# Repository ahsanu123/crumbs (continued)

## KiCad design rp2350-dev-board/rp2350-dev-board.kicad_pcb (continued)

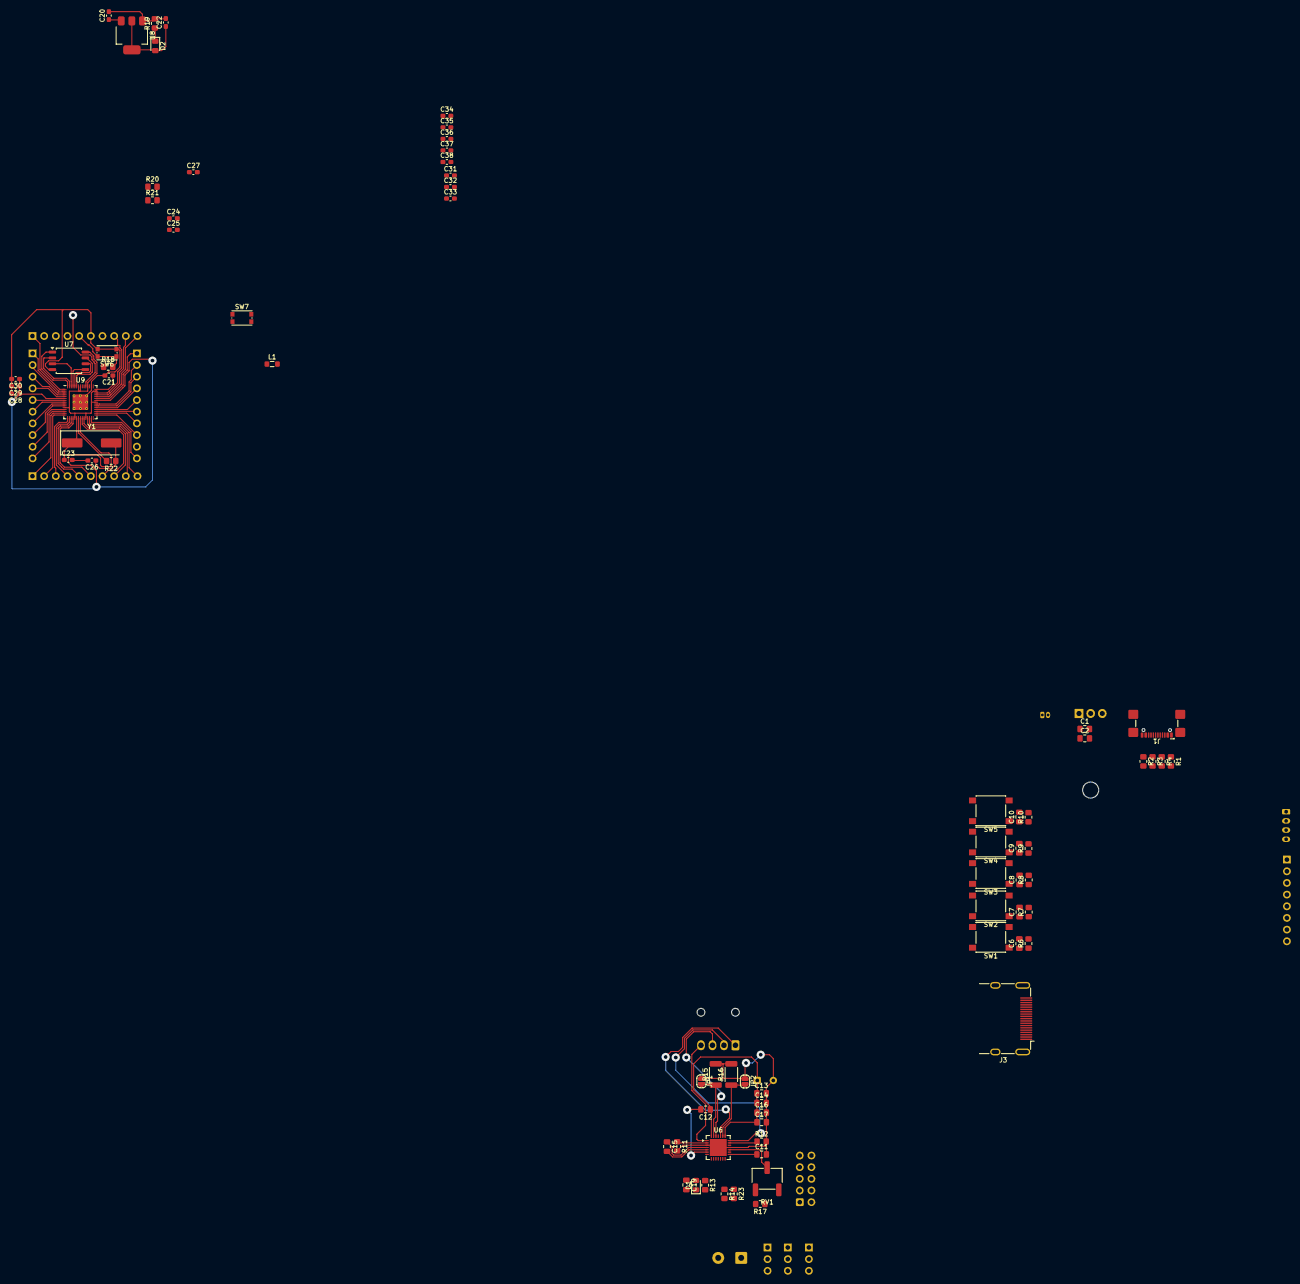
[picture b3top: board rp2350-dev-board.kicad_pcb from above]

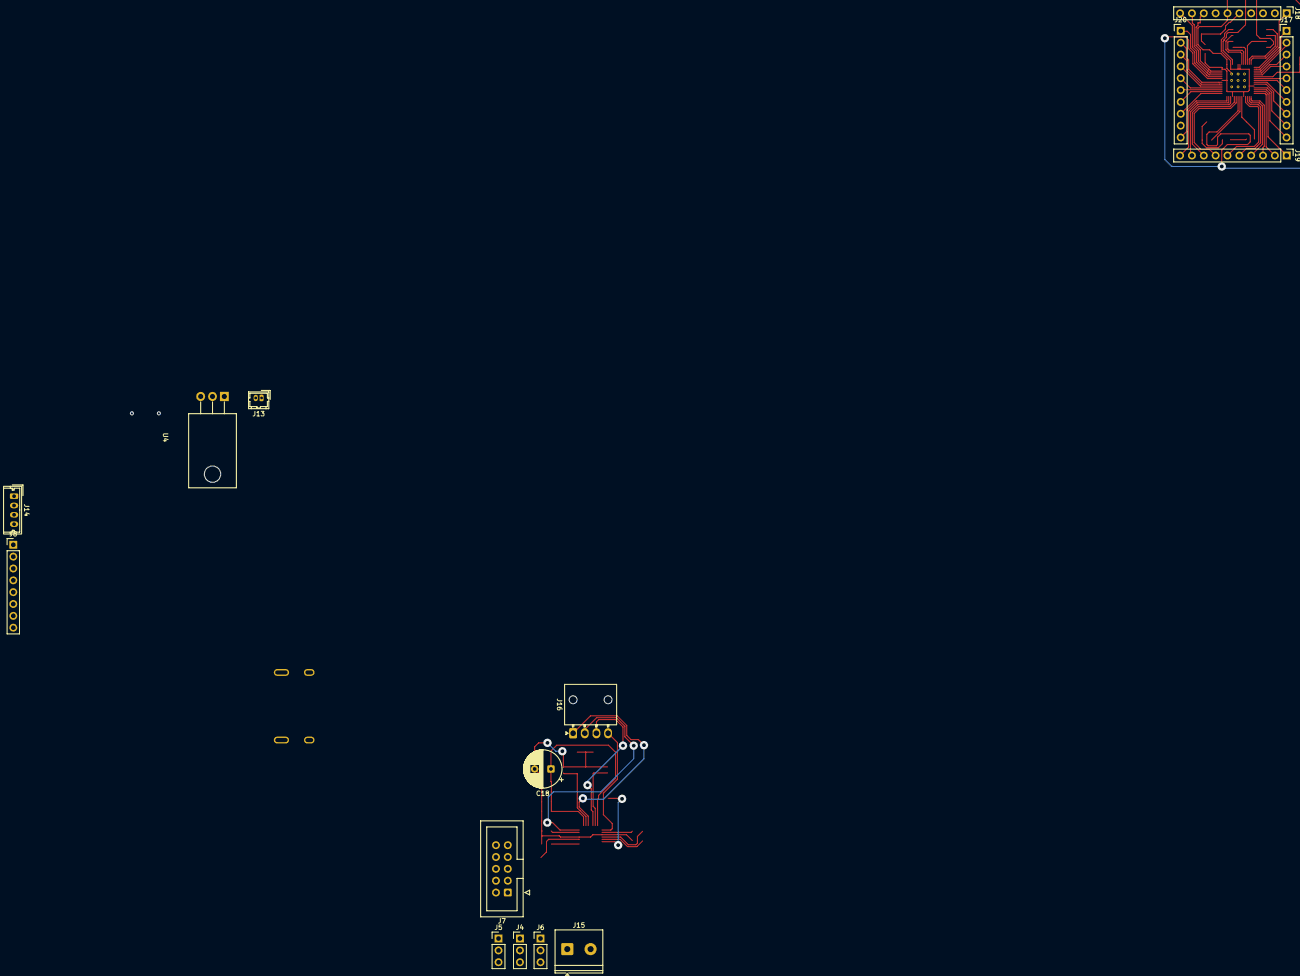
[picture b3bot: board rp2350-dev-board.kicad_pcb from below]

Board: 2 copper layers, 91 parts (15 on the bottom side), 83 nets.

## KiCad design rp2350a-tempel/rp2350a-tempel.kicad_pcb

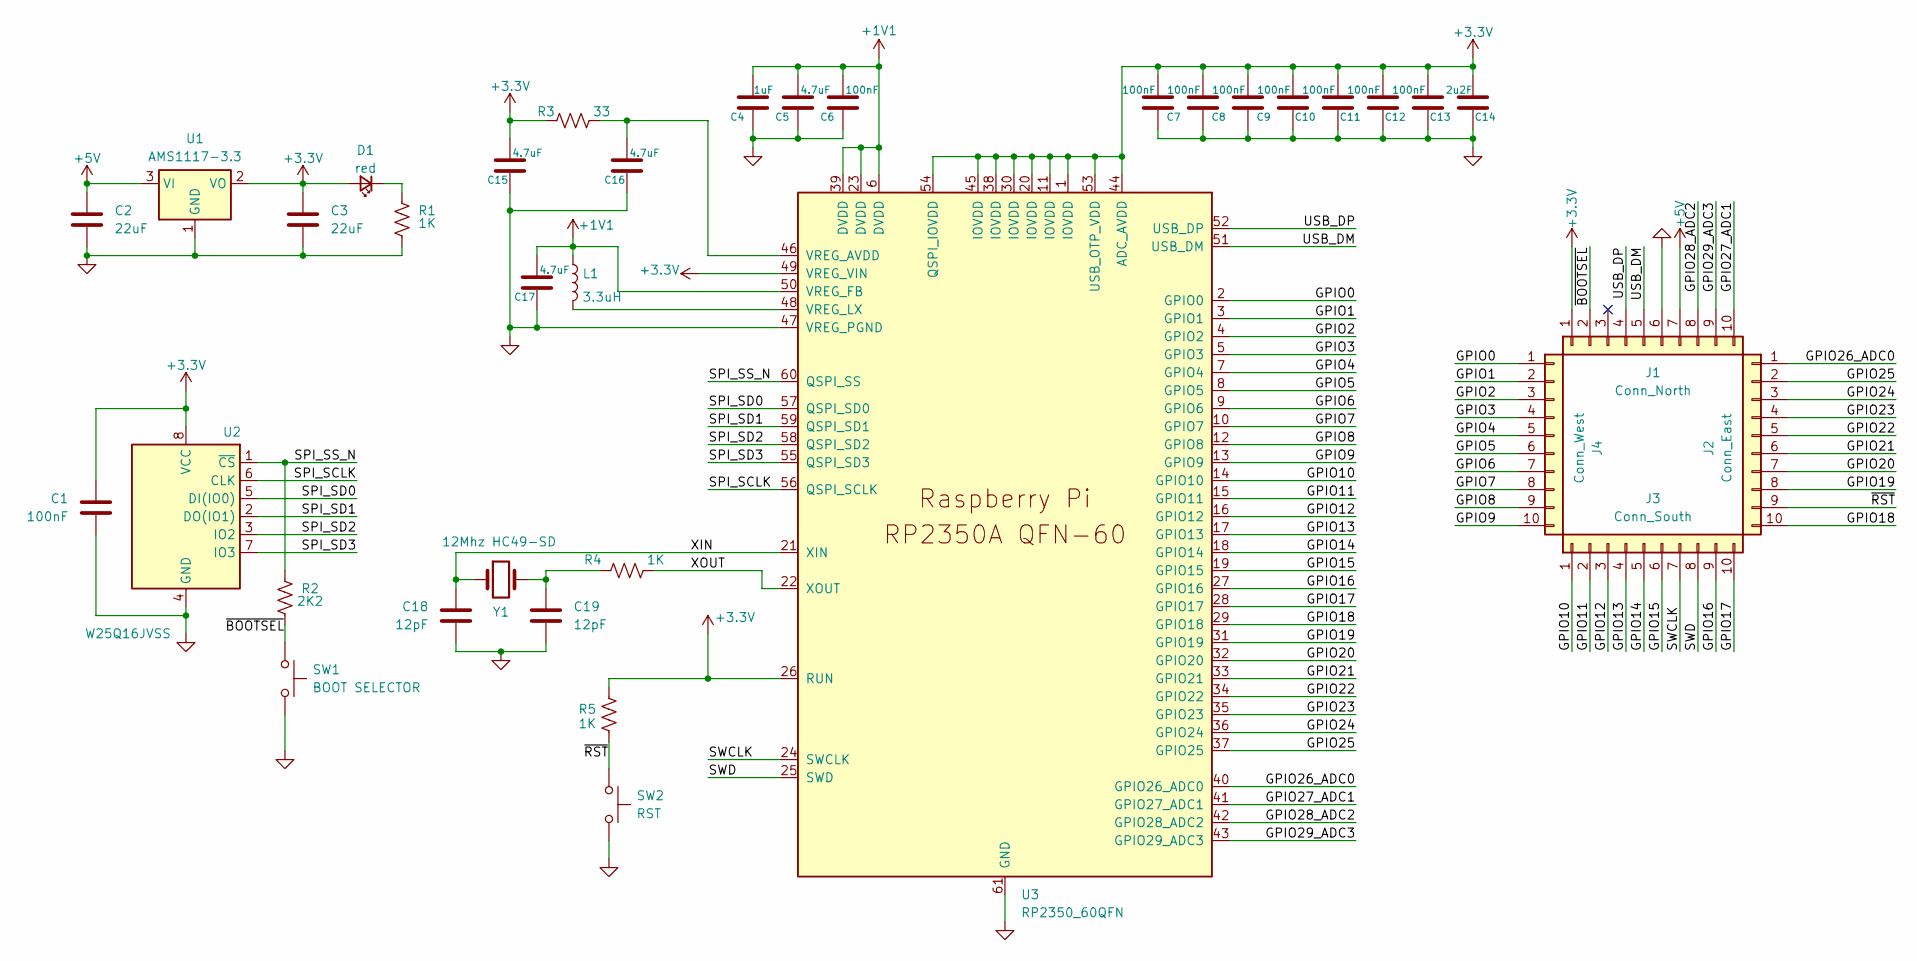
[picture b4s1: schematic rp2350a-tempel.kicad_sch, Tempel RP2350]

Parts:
C1, C6, C7, C8, C9, C10, C11, C12, C13: 100nF; C_0603_1608Metric_Pad1.08x0.95mm_HandSolder
C2, C3: 22uF; C_0603_1608Metric_Pad1.08x0.95mm_HandSolder
C4: 1uF; C_0603_1608Metric_Pad1.08x0.95mm_HandSolder
C5, C15, C16, C17: 4.7uF; C_0603_1608Metric_Pad1.08x0.95mm_HandSolder
C14: 2u2F; C_0603_1608Metric_Pad1.08x0.95mm_HandSolder
C18, C19: 12pF; C_0603_1608Metric_Pad1.08x0.95mm_HandSolder
D1: red; LED_0805_2012Metric_Pad1.15x1.40mm_HandSolder; mouser# 78-VLMS1300-GS08
J1: Conn_North; PinHeader_1x10_P2.54mm_Vertical
J2: Conn_East; PinHeader_1x10_P2.54mm_Vertical
J3: Conn_South; PinHeader_1x10_P2.54mm_Vertical
J4: Conn_West; PinHeader_1x10_P2.54mm_Vertical
L1: 3.3uH; L_0805_2012Metric_Pad1.15x1.40mm_HandSolder
R1, R4, R5: 1K; R_0805_2012Metric_Pad1.20x1.40mm_HandSolder
R2: 2K2; R_0805_2012Metric_Pad1.20x1.40mm_HandSolder
R3: 33; R_0805_2012Metric_Pad1.20x1.40mm_HandSolder
SW1: BOOT SELECTOR; SW_Push_1P1T_NO_CK_KMR2
SW2: RST; SW_Push_1P1T_NO_CK_KMR2
U1: AMS1117-3.3; SOT-223-3_TabPin2
U2: W25Q16JVSS; SOIC-8_5.23x5.23mm_P1.27mm
U3: RP2350_60QFN; RP2350-QFN-60-1EP_7x7_P0.4mm_EP3.4x3.4mm_ThermalVias
Y1: 12Mhz HC49-SD; Crystal_SMD_HC49-SD

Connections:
+1V1: C4.1, C5.1, C6.1, C17.1, L1.1, U3.6 (DVDD), U3.23 (DVDD), U3.39 (DVDD), U3.50 (VREG_FB)
+3.3V: C1.1, C3.1, C7.1, C8.1, C9.1, C10.1, C11.1, C12.1, C13.1, C14.1, C15.1, D1.2 (A), J1.1, R3.1, R5.2, U1.2 (VO), U2.8 (VCC), U3.1 (IOVDD), U3.11 (IOVDD), U3.20 (IOVDD), U3.26 (RUN), U3.30 (IOVDD), U3.38 (IOVDD), U3.44 (ADC_AVDD), U3.45 (IOVDD), U3.49 (VREG_VIN), U3.53 (USB_OTP_VDD), U3.54 (QSPI_IOVDD)
+5V: C2.1, J1.7, U1.3 (VI)
/GPIO0: J4.1, U3.2 (GPIO0)
/GPIO1: J4.2, U3.3 (GPIO1)
/GPIO2: J4.3, U3.4 (GPIO2)
/GPIO3: J4.4, U3.5 (GPIO3)
/GPIO4: J4.5, U3.7 (GPIO4)
/GPIO5: J4.6, U3.8 (GPIO5)
/GPIO6: J4.7, U3.9 (GPIO6)
/GPIO7: J4.8, U3.10 (GPIO7)
/GPIO8: J4.9, U3.12 (GPIO8)
/GPIO9: J4.10, U3.13 (GPIO9)
/GPIO10: J3.1, U3.14 (GPIO10)
/GPIO11: J3.2, U3.15 (GPIO11)
/GPIO12: J3.3, U3.16 (GPIO12)
/GPIO13: J3.4, U3.17 (GPIO13)
/GPIO14: J3.5, U3.18 (GPIO14)
/GPIO15: J3.6, U3.19 (GPIO15)
/GPIO16: J3.9, U3.27 (GPIO16)
/GPIO17: J3.10, U3.28 (GPIO17)
/GPIO18: J2.10, U3.29 (GPIO18)
/GPIO19: J2.8, U3.31 (GPIO19)
/GPIO20: J2.7, U3.32 (GPIO20)
/GPIO21: J2.6, U3.33 (GPIO21)
/GPIO22: J2.5, U3.34 (GPIO22)
/GPIO23: J2.4, U3.35 (GPIO23)
/GPIO24: J2.3, U3.36 (GPIO24)
/GPIO25: J2.2, U3.37 (GPIO25)
/GPIO26_ADC0: J2.1, U3.40 (GPIO26_ADC0)
/GPIO27_ADC1: J1.10, U3.41 (GPIO27_ADC1)
/GPIO28_ADC2: J1.8, U3.42 (GPIO28_ADC2)
/GPIO29_ADC3: J1.9, U3.43 (GPIO29_ADC3)
/SPI_SCLK: U2.6 (CLK), U3.56 (QSPI_SCLK)
/SPI_SD0: U2.5 (DI(IO0)), U3.57 (QSPI_SD0)
/SPI_SD1: U2.2 (DO(IO1)), U3.59 (QSPI_SD1)
/SPI_SD2: U2.3 (IO2), U3.58 (QSPI_SD2)
/SPI_SD3: U2.7 (IO3), U3.55 (QSPI_SD3)
/SPI_SS_N: R2.1, U2.1 (~CS), U3.60 (QSPI_SS)
/SWCLK: J3.7, U3.24 (SWCLK)
/SWD: J3.8, U3.25 (SWD)
/USB_DM: J1.5, U3.51 (USB_DM)
/USB_DP: J1.4, U3.52 (USB_DP)
/XIN: C18.1, U3.21 (XIN), Y1.1
/XOUT: R4.2, U3.22 (XOUT)
/~BOOTSEL: J1.2, R2.2, SW1.1
/~RST: J2.9, R5.1, SW2.1
GND: C1.2, C2.2, C3.2, C4.2, C5.2, C6.2, C7.2, C8.2, C9.2, C10.2, C11.2, C12.2, C13.2, C14.2, C15.2, C16.2, C17.2, C18.2, C19.2, J1.6, R1.2, SW1.2, SW2.2, U1.1 (GND), U2.4 (GND), U3.47 (VREG_PGND), U3.61 (GND)
unnamed: C19.1, R4.1, Y1.2
unnamed: D1.1 (K), R1.1
unnamed: C16.1, R3.2, U3.46 (VREG_AVDD)
unnamed: L1.2, U3.48 (VREG_LX)

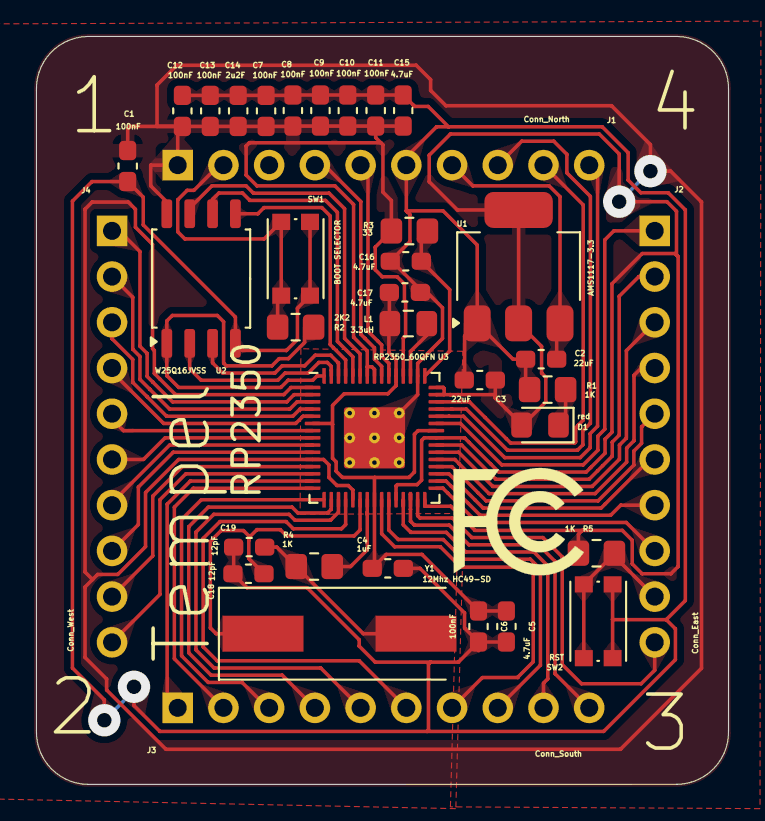
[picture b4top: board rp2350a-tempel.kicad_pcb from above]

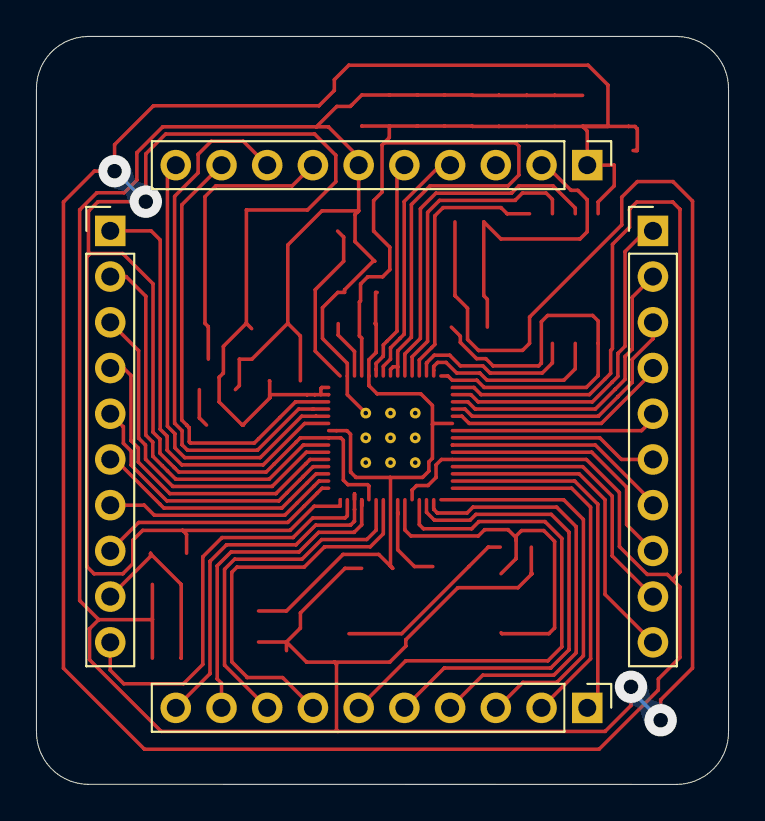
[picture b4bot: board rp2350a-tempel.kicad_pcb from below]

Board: 2 copper layers, 38.4 x 41.6 mm, 36 parts (4 on the bottom side), 52 nets.

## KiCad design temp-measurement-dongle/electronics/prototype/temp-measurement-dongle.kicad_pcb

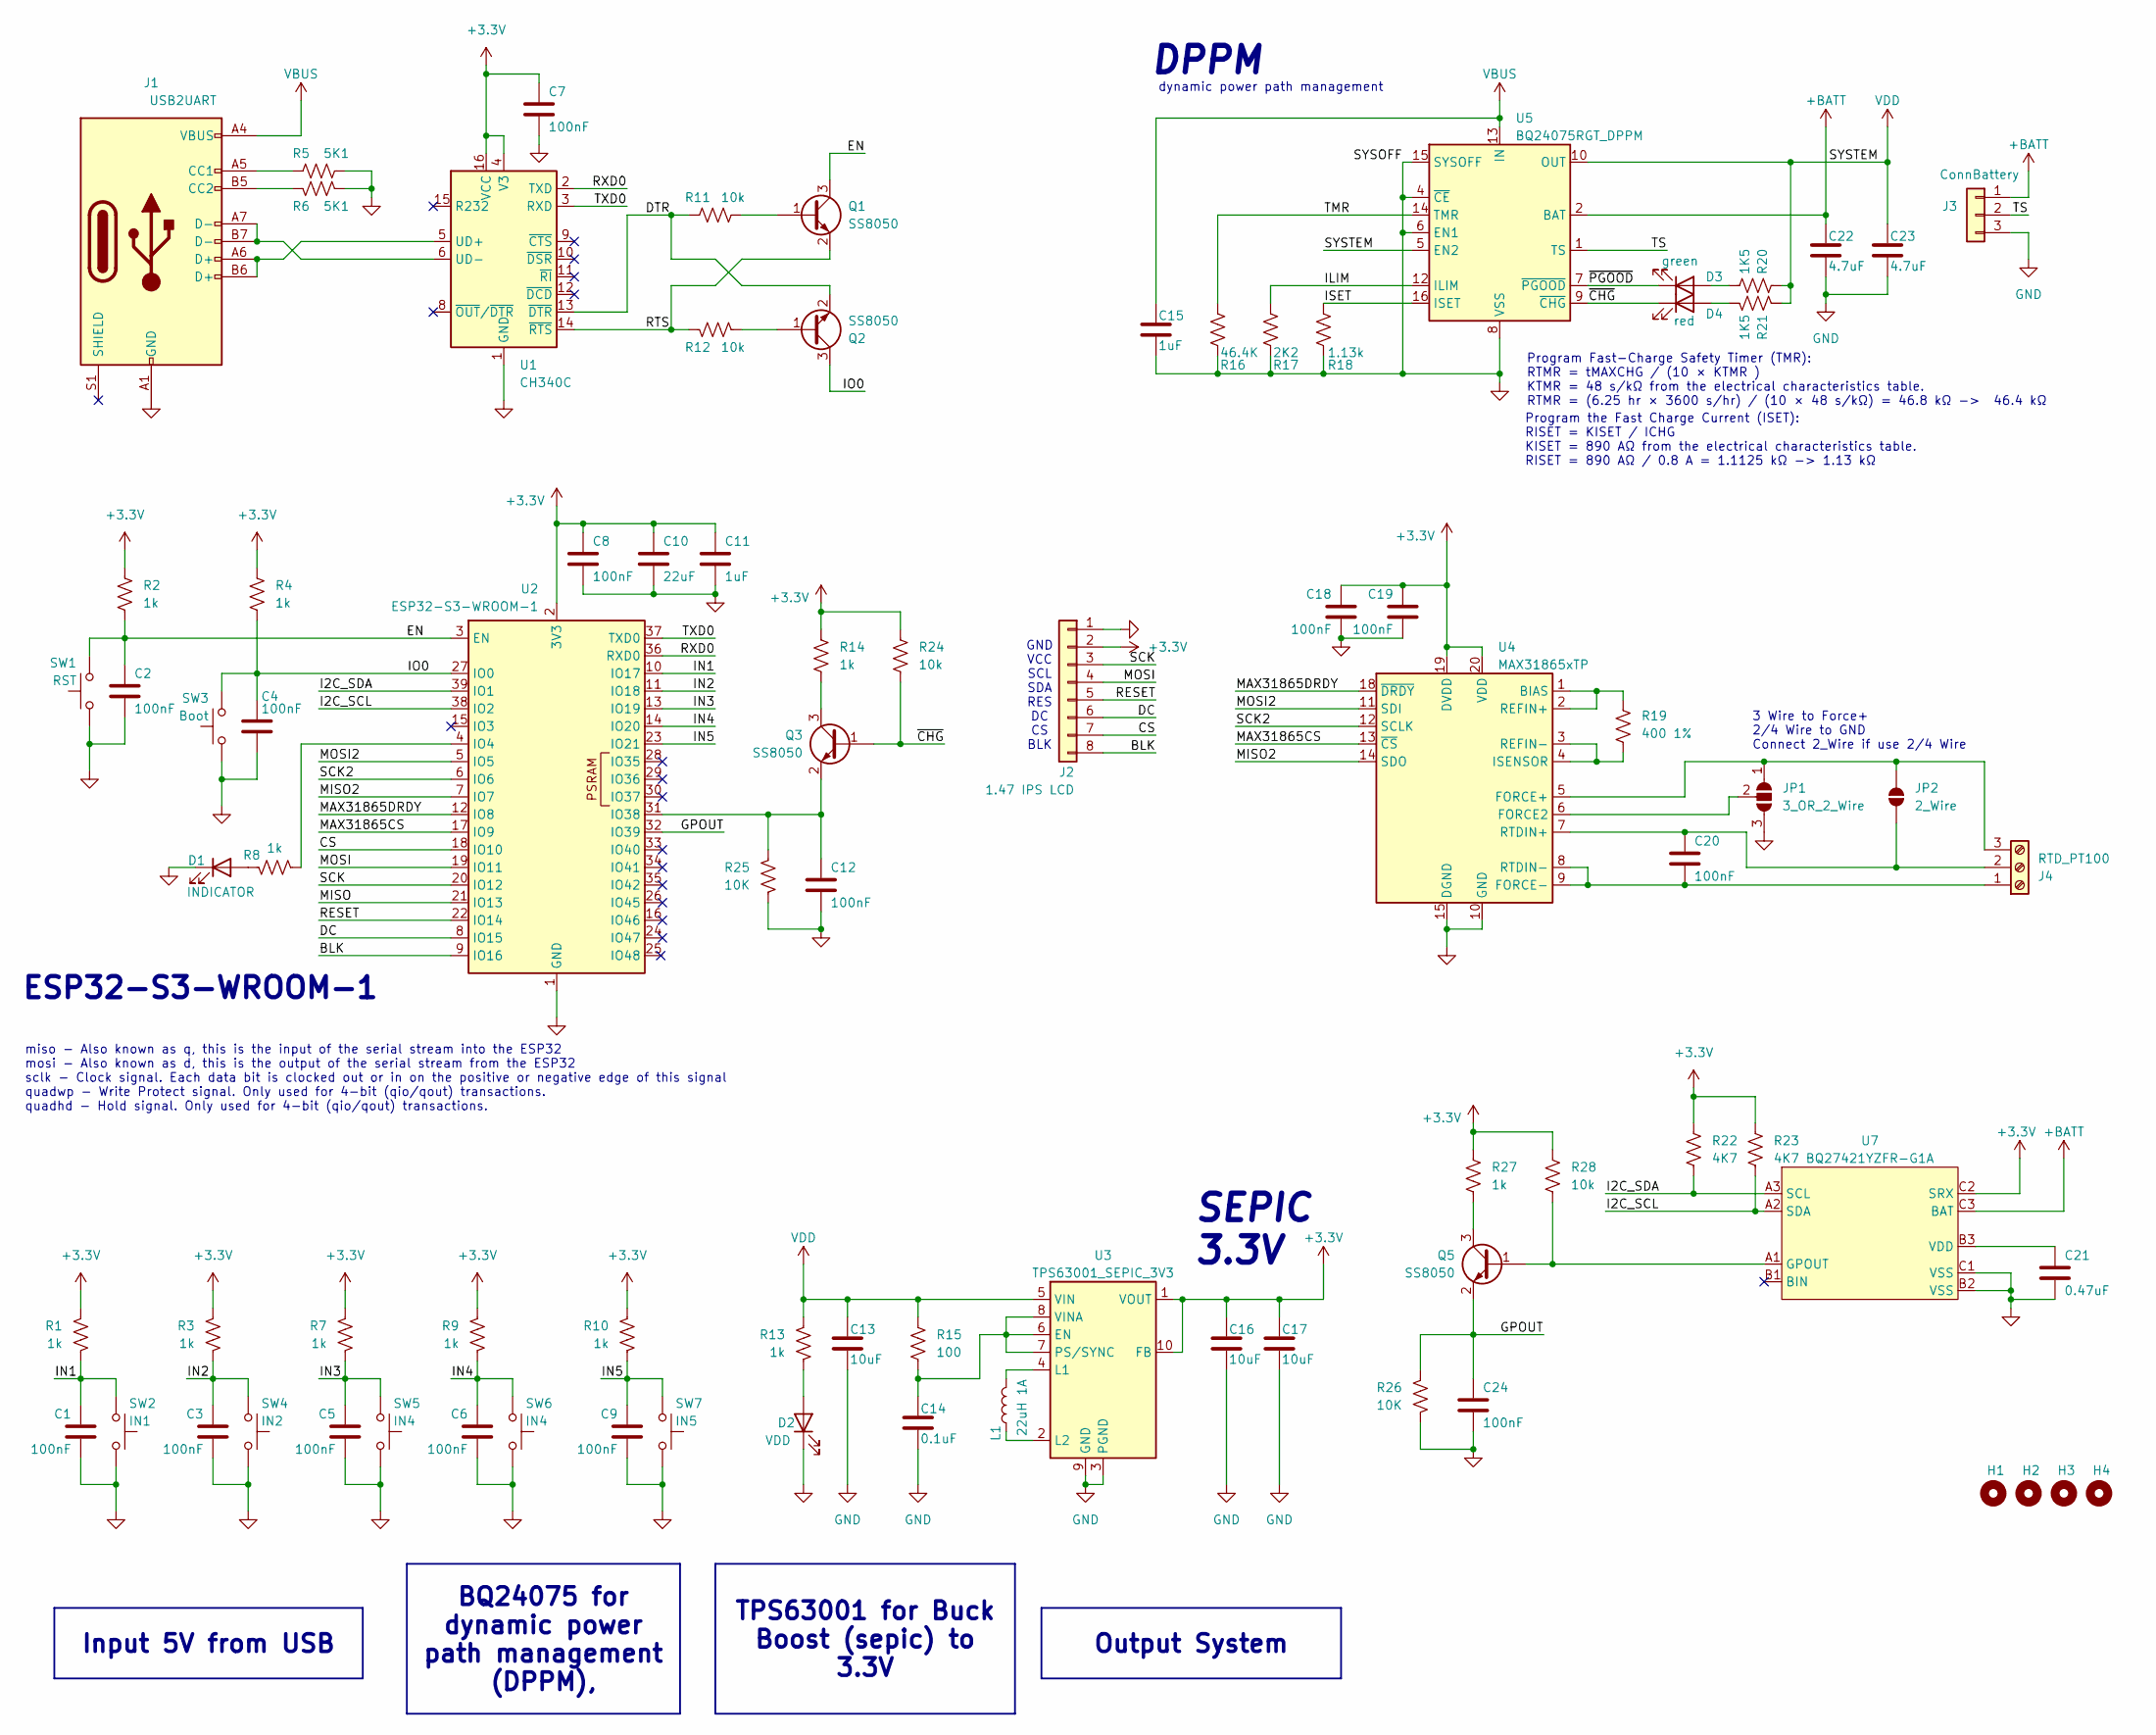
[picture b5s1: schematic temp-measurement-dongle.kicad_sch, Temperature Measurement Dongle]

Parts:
C1, C2, C3, C4, C5, C6, C7, C8, C9, C12, C18, C19, C20, C24: 100nF; C_0805_2012Metric_Pad1.18x1.45mm_HandSolder
C10: 22uF; C_0805_2012Metric_Pad1.18x1.45mm_HandSolder
C11, C15: 1uF; C_0805_2012Metric_Pad1.18x1.45mm_HandSolder
C13, C16, C17: 10uF; C_0805_2012Metric_Pad1.18x1.45mm_HandSolder
C14: 0.1uF; C_0805_2012Metric_Pad1.18x1.45mm_HandSolder
C21: 0.47uF; C_0805_2012Metric_Pad1.18x1.45mm_HandSolder
C22, C23: 4.7uF; C_0805_2012Metric_Pad1.18x1.45mm_HandSolder
D1: INDICATOR; LED_1206_3216Metric_Pad1.42x1.75mm_HandSolder
D2: VDD; LED_1206_3216Metric_Pad1.42x1.75mm_HandSolder
D3: green; LED_0805_2012Metric_Pad1.15x1.40mm_HandSolder
D4: red; LED_0805_2012Metric_Pad1.15x1.40mm_HandSolder
H1, H2, H3, H4: MountingHole; MountingHole_2mm
J1: USB2UART; USB_C_Receptacle_GCT_USB4110
J2: 1.47 IPS LCD; PinHeader_1x08_P2.54mm_Vertical
J3: ConnBattery; PinHeader_1x03_P2.54mm_Vertical
J4: RTD_PT100; TerminalBlock_Phoenix_PT-1,5-3-5.0-H_1x03_P5.00mm_Horizontal
JP1: 3_OR_2_Wire; SolderJumper-3_P1.3mm_Open_RoundedPad1.0x1.5mm
JP2: 2_Wire; SolderJumper-2_P1.3mm_Open_TrianglePad1.0x1.5mm
L1: 22uH 1A; L_Bourns_SRP7028A_7.3x6.6mm
Q1, Q2, Q3, Q5: SS8050; SOT-23_Handsoldering
R1, R2, R3, R4, R7, R8, R9, R10, R13, R14, R27: 1k; R_0805_2012Metric_Pad1.20x1.40mm_HandSolder
R5, R6: 5K1; R_0805_2012Metric_Pad1.20x1.40mm_HandSolder
R11, R12, R24, R28: 10k; R_0805_2012Metric_Pad1.20x1.40mm_HandSolder
R15: 100; R_0805_2012Metric_Pad1.20x1.40mm_HandSolder
R16: 46.4K; R_0805_2012Metric_Pad1.20x1.40mm_HandSolder
R17: 2K2; R_0805_2012Metric_Pad1.20x1.40mm_HandSolder
R18: 1.13k; R_0805_2012Metric_Pad1.20x1.40mm_HandSolder
R19: 400 1%; R_0805_2012Metric_Pad1.20x1.40mm_HandSolder
R20, R21: 1K5; R_0805_2012Metric_Pad1.20x1.40mm_HandSolder
R22, R23: 4K7; R_0805_2012Metric_Pad1.20x1.40mm_HandSolder
R25, R26: 10K; R_0805_2012Metric_Pad1.20x1.40mm_HandSolder
SW1: RST; SW_SPST_PTS810
SW2: IN1; SW_SPST_Omron_B3FS-100xP
SW3: Boot; SW_SPST_PTS810
SW4: IN2; SW_SPST_Omron_B3FS-100xP
SW5, SW6: IN4; SW_SPST_Omron_B3FS-100xP
SW7: IN5; SW_SPST_Omron_B3FS-100xP
U1: CH340C; SOIC-16_3.9x9.9mm_P1.27mm
U2: ESP32-S3-WROOM-1
U3: TPS63001_SEPIC_3V3; Texas_DRC0010J_ThermalVias
U4: MAX31865xTP; TQFN-20-1EP_5x5mm_P0.65mm_EP3.25x3.25mm
U5: BQ24075RGT_DPPM; VQFN-16-1EP_3x3mm_P0.5mm_EP1.6x1.6mm
U7: BQ27421YZFR-G1A; DSBGA-9_L1.5-W1.5-R3-C3-P0.50-BL; MPN BQ27421YZFR-G1A; LCSC Part C139621

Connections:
+3.3V: C7.1, C8.1, C10.1, C11.1, C16.1, C17.1, C18.1, C19.1, J2.2, R1.1, R2.1, R3.1, R4.1, R7.1, R9.1, R10.1, R14.1, R22.1, R23.1, R24.1, R27.1, R28.1, U1.4 (V3), U1.16 (VCC), U2.2 (3V3), U3.1 (VOUT), U3.10 (FB), U4.19 (DVDD), U4.20 (VDD), U7.C2 (SRX)
+BATT: C22.1, J3.1, U5.2 (BAT), U5.3 (BAT), U7.C3 (BAT)
/BLK: J2.8, U2.9 (IO16)
/CS: J2.7, U2.18 (IO10)
/DC: J2.6, U2.8 (IO15)
/DTR: Q2.2 (E), R11.2, U1.13 (~DTR)
/EN: C2.1, Q1.3 (C), R2.2, SW1.2, U2.3 (EN)
/GPOUT: C24.1, Q5.2 (E), R26.1, U2.32 (IO39)
/I2C_SCL: R23.2, U2.38 (IO2), U7.A2 (SDA)
/I2C_SDA: R22.2, U2.39 (IO1), U7.A3 (SCL)
/ILIM: R17.1, U5.12 (ILIM)
/IN1: C1.1, R1.2, SW2.2, U2.10 (IO17)
/IN2: C3.1, R3.2, SW4.2, U2.11 (IO18)
/IN3: C5.1, R7.2, SW5.2, U2.13 (IO19)
/IN4: C6.1, R9.2, SW6.2, U2.14 (IO20)
/IN5: C9.1, R10.2, SW7.2, U2.23 (IO21)
/IO0: C4.1, Q2.3 (C), R4.2, SW3.2, U2.27 (IO0)
/ISET: R18.1, U5.16 (ISET)
/MAX31865CS: U2.17 (IO9), U4.13 (~CS)
/MAX31865DRDY: U2.12 (IO8), U4.18 (~DRDY)
/MISO: U2.21 (IO13)
/MISO2: U2.7 (IO7), U4.14 (SDO)
/MOSI: J2.4, U2.19 (IO11)
/MOSI2: U2.5 (IO5), U4.11 (SDI)
/RESET: J2.5, U2.22 (IO14)
/RTS: Q1.2 (E), R12.2, U1.14 (~RTS)
/RXD0: U1.2 (TXD), U2.36 (RXD0)
/SCK: J2.3, U2.20 (IO12)
/SCK2: U2.6 (IO6), U4.12 (SCLK)
/TMR: R16.1, U5.14 (TMR)
/TS: J3.2, U5.1 (TS)
/TXD0: U1.3 (RXD), U2.37 (TXD0)
/~CHG: D4.1 (K), Q3.1 (B), R24.2, U5.9 (~CHG)
/~PGOOD: D3.1 (K), U5.7 (~PGOOD)
GND: C1.2, C2.2, C3.2, C4.2, C5.2, C6.2, C7.2, C8.2, C9.2, C10.2, C11.2, C12.2, C13.2, C14.2, C15.2, C16.2, C17.2, C18.2, C19.2, C21.2, C22.2, C23.2, C24.2, D1.1 (K), D2.1 (K), J1.A1 (GND), J1.A12 (GND), J1.B1 (GND), J1.B12 (GND), J2.1, J3.3, JP1.3 (B), R5.1, R6.1, R16.2, R17.2, R18.2, R25.2, R26.2, SW1.1, SW2.1, SW3.1, SW4.1, SW5.1, SW6.1, SW7.1, U1.1 (GND), U2.1 (GND), U2.40 (GND), U2.41 (GND), U3.3 (PGND), U3.9 (GND), U3.11 (PGND), U4.10 (GND), U4.15 (DGND), U4.16 (GND), U4.21 (GND), U5.4 (~CE), U5.6 (EN1), U5.8 (VSS), U5.15 (SYSOFF), U5.17 (VSS), U7.B2 (VSS), U7.C1 (VSS); also elsewhere on the board
unnamed 35: D1.2 (A), R8.1; also elsewhere on the board
unnamed: D2.2 (A), R13.2
unnamed: D3.2 (A), R20.1
unnamed: D4.2 (A), R21.1
unnamed: J1.A5 (CC1), R5.2
unnamed: J1.B5 (CC2), R6.2
unnamed: C20.2, J4.1, U4.8 (RTDIN-), U4.9 (FORCE-)
unnamed: C20.1, J4.2, JP2.1 (A), U4.7 (RTDIN+)
unnamed: J4.3, JP1.1 (A), JP2.2 (B), U4.5 (FORCE+)
unnamed: JP1.2 (C), U4.6 (FORCE2)
unnamed: Q1.1 (B), R11.1
unnamed: Q2.1 (B), R12.1
unnamed: Q3.3 (C), R14.2
unnamed: C12.1, Q3.2 (E), R25.1, U2.31 (IO38)
unnamed: Q5.1 (B), R28.2, U7.A1 (GPOUT)
unnamed: Q5.3 (C), R27.2
unnamed: J1.A6 (D+), J1.B6 (D+), U1.5 (UD+)
unnamed: J1.A7 (D-), J1.B7 (D-), U1.6 (UD-)
unnamed 53: R8.2, U2.4 (IO4); also elsewhere on the board
unnamed: C14.1, R15.2, U3.6 (EN), U3.7 (PS/SYNC), U3.8 (VINA)
unnamed: L1.2, U3.4 (L1)
unnamed: L1.1, U3.2 (L2)
unnamed: R19.1, U4.1 (BIAS), U4.2 (REFIN+)
unnamed: R19.2, U4.3 (REFIN-), U4.4 (ISENSOR)
unnamed: C21.1, U7.B3 (VDD)
VBUS: C15.1, J1.A4 (VBUS), J1.A9 (VBUS), J1.B4 (VBUS), J1.B9 (VBUS), U5.13 (IN)
VDD: C13.1, C23.1, R13.1, R15.1, R20.2, R21.2, U3.5 (VIN), U5.5 (EN2), U5.10 (OUT), U5.11 (OUT)

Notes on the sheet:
dynamic power path management
GND VCC SCL SDA RES DC CS BLK
miso - Also known as q, this is the input of the serial stream into the ESP32 mosi - Also known as d, this is the output of the serial stream from the ESP32 sclk - Clock signal. Each data bit is clocked out or in on the positive or negative edge of this signal quadwp - Write Protect signal. Only us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
ESP32-S3-WROOM-1
Program the Fast Charge Current (ISET): RISET = KISET / ICHG KISET = 890 AΩ from the electrical characteristics table. RISET = 890 AΩ / 0.8 A = 1.1125 kΩ -> 1.13 kΩ
DPPM
3 Wire to Force+ 2/4 Wire to GND Connect 2_Wire if use 2/4 Wire
SEPIC 3.3V
Program Fast-Charge Safety Timer (TMR): RTMR = tMAXCHG / (10 × KTMR ) KTMR = 48 s/kΩ from the electrical characteristics table. RTMR = (6.25 hr × 3600 s/hr) / (10 × 48 s/kΩ) = 46.8 kΩ -> 46.4 kΩ
Output System
TPS63001 for Buck Boost (sepic) to 3.3V
Input 5V from USB
BQ24075 for dynamic power path management (DPPM),

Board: 2 copper layers, 86 parts (18 on the bottom side), 61 nets, no tracks yet.

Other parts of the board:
D1#2: INDICATOR; LED_1206_3216Metric_Pad1.42x1.75mm_HandSolder
R8#2: 1k; R_0805_2012Metric_Pad1.20x1.40mm_HandSolder

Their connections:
GND: D1#2.1 (K); also elsewhere on the board
unnamed 35: D1#2.2 (A), R8#2.1; also elsewhere on the board
unnamed 53: R8#2.2; also elsewhere on the board

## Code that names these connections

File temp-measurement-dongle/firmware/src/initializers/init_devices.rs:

use crate::display_models::st7735s_modified::ST7735s;
use crate::platforms::esp32s3_async::draw_buffer::DrawBuffer;
use crate::{DISPLAY_HEIGHT, DISPLAY_WIDTH, LCD_DEV_INTERFACE_BUFFER};
use core::cell::RefCell;
use critical_section::Mutex;
use embedded_hal_bus::spi::CriticalSectionDevice;
use esp_hal::delay::Delay;
use esp_hal::dma::{DmaRxBuf, DmaTxBuf};
use esp_hal::gpio::{Input, InputConfig, Level, Output, OutputConfig, Pull};
use esp_hal::peripherals::Peripherals;
use esp_hal::spi::Mode;
use esp_hal::spi::master::Spi;
use esp_hal::spi::master::{Config, SpiDmaBus};
use esp_hal::time::Rate;
use esp_hal::timer::timg::TimerGroup;
use esp_hal::{Blocking, dma_buffers};
use max31865::{Max31865, Numwires};
use mipidsi::Display;
use mipidsi::interface::SpiInterface;
use mipidsi::options::{ColorOrder, Orientation, Rotation};
use static_cell::StaticCell;

pub static MUTEX_SPI_BUS: StaticCell<Mutex<RefCell<SpiDmaBus<'static, Blocking>>>> =
    StaticCell::new();

pub type DrawBufferType = DrawBuffer<
    Display<
        SpiInterface<
            'static,
            CriticalSectionDevice<'static, SpiDmaBus<'static, Blocking>, Output<'static>, Delay>,
            Output<'static>,
        >,
        ST7735s,
        Output<'static>,
    >,
>;

pub type Max31865Type = Max31865<
    CriticalSectionDevice<'static, SpiDmaBus<'static, Blocking>, Output<'static>, Delay>,
    Delay,
>;

pub fn init_devices(
    peripherals: Peripherals,
) -> (
    Input<'static>,
    Input<'static>,
    Input<'static>,
    Input<'static>,
    Input<'static>,
    DrawBufferType,
    Output<'static>,
    Max31865Type,
) {
    let timg0 = TimerGroup::new(peripherals.TIMG0);
    esp_rtos::start(timg0.timer0);

    let input_up = peripherals.GPIO17;
    let input_right = peripherals.GPIO20;
    let input_bottom = peripherals.GPIO19;
    let input_left = peripherals.GPIO18;

    let input_is_charging = peripherals.GPIO38;

    let lcd_dc = peripherals.GPIO15;
    let lcd_cs = peripherals.GPIO10;
    let lcd_rst = peripherals.GPIO14;
    let lcd_blk = peripherals.GPIO16;

    let scl_mosi = peripherals.GPIO11;
    let scl_sck = peripherals.GPIO12;
    let scl_miso = peripherals.GPIO13;

    let max31865_cs = peripherals.GPIO9;
    let max31865_drdy = peripherals.GPIO8;

    let dma_channel = peripherals.DMA_CH0;

    let key_up = Input::new(input_up, InputConfig::default().with_pull(Pull::Up));
    let key_right = Input::new(input_right, InputConfig::default().with_pull(Pull::Up));
    let key_down = Input::new(input_bottom, InputConfig::default().with_pull(Pull::Up));
    let key_left = Input::new(input_left, InputConfig::default().with_pull(Pull::Up));

    let input_is_charging = Input::new(
        input_is_charging,
        InputConfig::default().with_pull(Pull::Up),
    );

    let lcd_cs = Output::new(lcd_cs, Level::Low, OutputConfig::default());
    let lcd_dc = Output::new(lcd_dc, Level::Low, OutputConfig::default());
    let lcd_rst = Output::new(lcd_rst, Level::Low, OutputConfig::default());
    let lcd_blk = Output::new(lcd_blk, Level::Low, OutputConfig::default());

    let (rx_buffer, rx_descriptors, tx_buffer, tx_descriptors) = dma_buffers!(2048);
    let dma_rx_buf = DmaRxBuf::new(rx_descriptors, rx_buffer).unwrap();
    let dma_tx_buf = DmaTxBuf::new(tx_descriptors, tx_buffer).unwrap();

    let max31865_cs = Output::new(max31865_cs, Level::Low, OutputConfig::default());
    let _max31865_drdy = Input::new(max31865_drdy, InputConfig::default().with_pull(Pull::Up));

    let spi_bus = Spi::new(
        peripherals.SPI2,
        Config::default()
            .with_frequency(Rate::from_mhz(5))
            .with_mode(Mode::_1),
    )
    .unwrap()
    .with_sck(scl_sck)
    .with_mosi(scl_mosi)
    .with_miso(scl_miso)
    .with_dma(dma_channel)
    .with_buffers(dma_rx_buf, dma_tx_buf);

    let lcd_dev_interface_buffer = LCD_DEV_INTERFACE_BUFFER.init([0u8; 312]);

    let mut delay = Delay::new();
    let mutex_refcell_bus = MUTEX_SPI_BUS.init(Mutex::new(RefCell::new(spi_bus)));

    let lcd_spi_device = CriticalSectionDevice::new(mutex_refcell_bus, lcd_cs, delay).unwrap();

    let di =
        mipidsi::interface::SpiInterface::new(lcd_spi_device, lcd_dc, lcd_dev_interface_buffer);

    let st7735 = mipidsi::Builder::new(crate::display_models::st7735s_modified::ST7735s, di)
        .display_size(DISPLAY_WIDTH as u16, DISPLAY_HEIGHT as u16)
        .orientation(Orientation::new().rotate(Rotation::Deg90))
        .color_order(ColorOrder::Rgb)
        .display_offset(84, 0)
        .reset_pin(lcd_rst)
        .init(&mut delay)
        .expect("fail to build display st7735s");

    let draw_buffer = DrawBuffer::new(st7735);

    let max31865_spi_device =
        CriticalSectionDevice::new(mutex_refcell_bus, max31865_cs, delay).unwrap();

    let max31865 = Max31865::new(
        max31865_spi_device,
        delay,
        Numwires::MAX31865_3_WIRE,
        100.0,
        430.0,
    );

    (
        key_up,
        key_left,
        key_down,
        key_right,
        input_is_charging,
        draw_buffer,
        lcd_blk,
        max31865,
    )
}
